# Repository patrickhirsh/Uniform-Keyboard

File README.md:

# Uniform65 Keyboard
A custom semi-ortholinear stabless mechanical keyboard

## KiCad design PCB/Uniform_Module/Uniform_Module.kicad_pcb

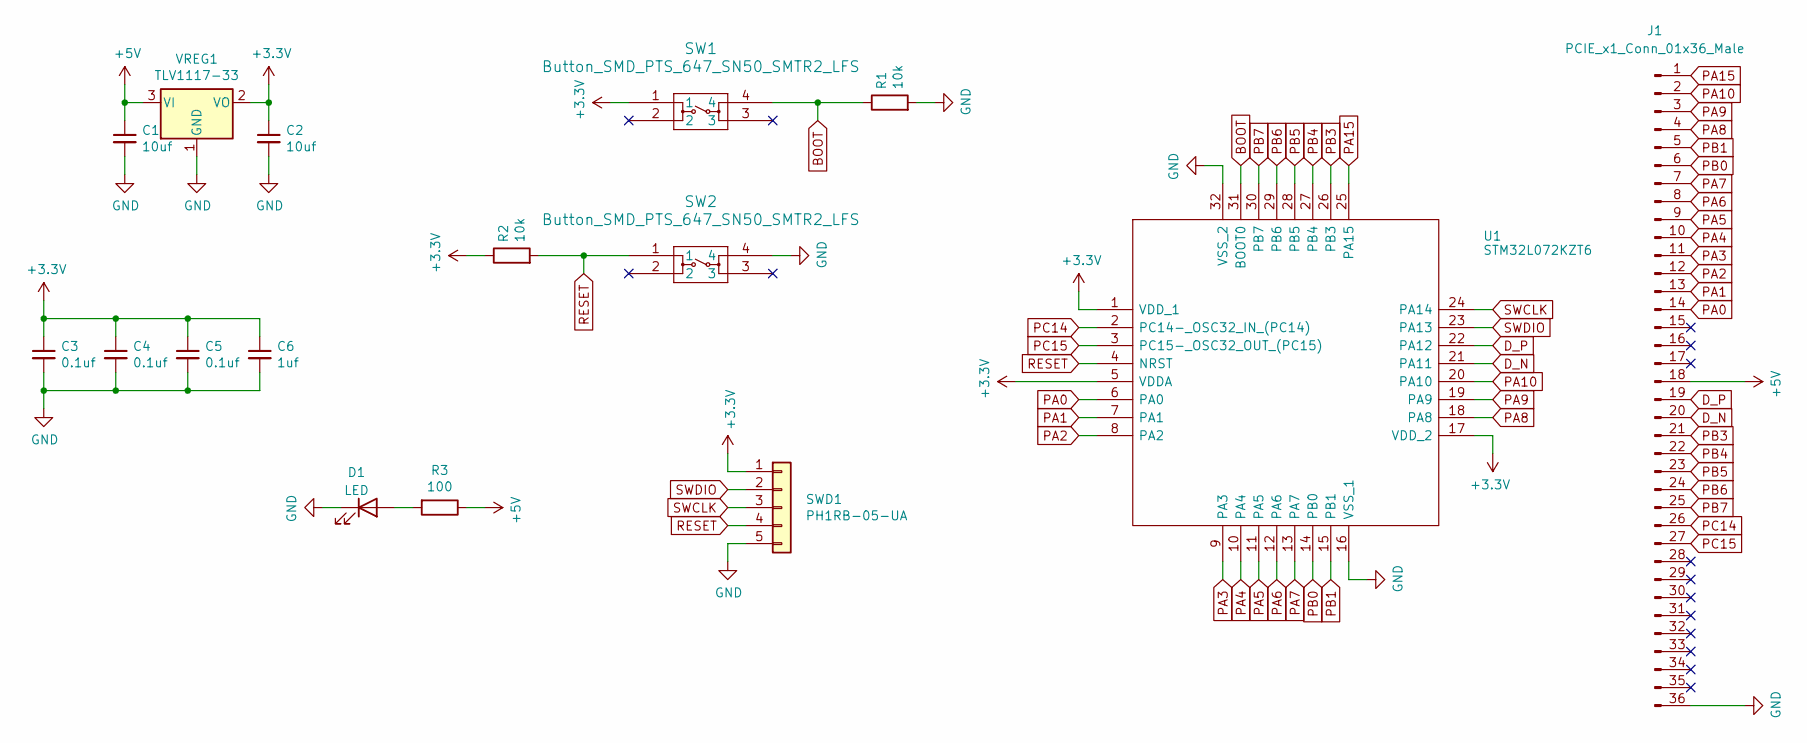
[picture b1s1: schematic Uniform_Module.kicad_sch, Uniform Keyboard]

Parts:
C1, C2: 10uf; C_0603_1608Metric_Pad1.08x0.95mm_HandSolder
C3, C4, C5: 0.1uf; C_0603_1608Metric_Pad1.08x0.95mm_HandSolder
C6: 1uf; C_0603_1608Metric_Pad1.08x0.95mm_HandSolder
D1: LED; LED_0603_1608Metric_Pad1.05x0.95mm_HandSolder
J1: PCIE_x1_Conn_01x36_Male; SAMTEC_PCIE_x1_CARD_EDGE_02_X_D_TH
R1, R2: 10k; R_0603_1608Metric_Pad0.98x0.95mm_HandSolder
R3: 100; R_0603_1608Metric_Pad0.98x0.95mm_HandSolder
SW1, SW2: Button_SMD_PTS_647_SN50_SMTR2_LFS; Button SMD PTS 647 SN50 SMTR2 LFS
SWD1: PH1RB-05-UA; PinHeader_1x05_P2.54mm_Vertical
U1: STM32L072KZT6; QFP80P900X900X160-32N; Mouser Part Number 511-STM32L072KZT6
VREG1: TLV1117-33; SOT230P700X180-4N

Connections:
+3V3: C2.1, C3.1, C4.1, C5.1, C6.1, R2.1, SW1.1, SWD1.1, U1.1 (VDD_1), U1.5 (VDDA), U1.17 (VDD_2), VREG1.2 (VO)
+5V: C1.1, J1.18, R3.1, VREG1.3 (VI)
BOOT: R1.1, SW1.4, U1.31 (BOOT0)
D_N: J1.20, U1.21 (PA11)
D_P: J1.19, U1.22 (PA12)
GND: C1.2, C2.2, C3.2, C4.2, C5.2, C6.2, D1.1 (K), J1.36, R1.2, SW2.4, SWD1.5, U1.16 (VSS_1), U1.32 (VSS_2), VREG1.1 (GND)
unnamed: D1.2 (A), R3.2
PA0: J1.14, U1.6 (PA0)
PA1: J1.13, U1.7 (PA1)
PA2: J1.12, U1.8 (PA2)
PA3: J1.11, U1.9 (PA3)
PA4: J1.10, U1.10 (PA4)
PA5: J1.9, U1.11 (PA5)
PA6: J1.8, U1.12 (PA6)
PA7: J1.7, U1.13 (PA7)
PA8: J1.4, U1.18 (PA8)
PA9: J1.3, U1.19 (PA9)
PA10: J1.2, U1.20 (PA10)
PA15: J1.1, U1.25 (PA15)
PB0: J1.6, U1.14 (PB0)
PB1: J1.5, U1.15 (PB1)
PB3: J1.21, U1.26 (PB3)
PB4: J1.22, U1.27 (PB4)
PB5: J1.23, U1.28 (PB5)
PB6: J1.24, U1.29 (PB6)
PB7: J1.25, U1.30 (PB7)
PC14: J1.26, U1.2 (PC14-_OSC32_IN_(PC14))
PC15: J1.27, U1.3 (PC15-_OSC32_OUT_(PC15))
RESET: R2.2, SW2.1, SWD1.4, U1.4 (NRST)
SWCLK: SWD1.3, U1.24 (PA14)
SWDIO: SWD1.2, U1.23 (PA13)

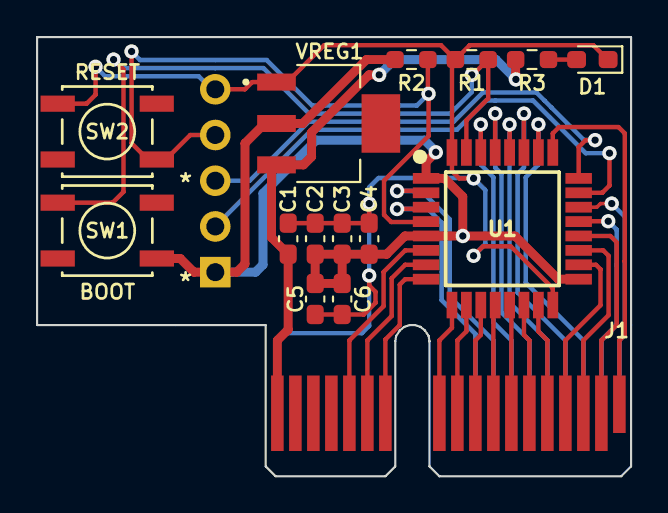
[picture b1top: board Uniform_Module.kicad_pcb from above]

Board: 2 copper layers, 33.0 x 24.4 mm, 16 parts (1 on the bottom side), 31 nets.

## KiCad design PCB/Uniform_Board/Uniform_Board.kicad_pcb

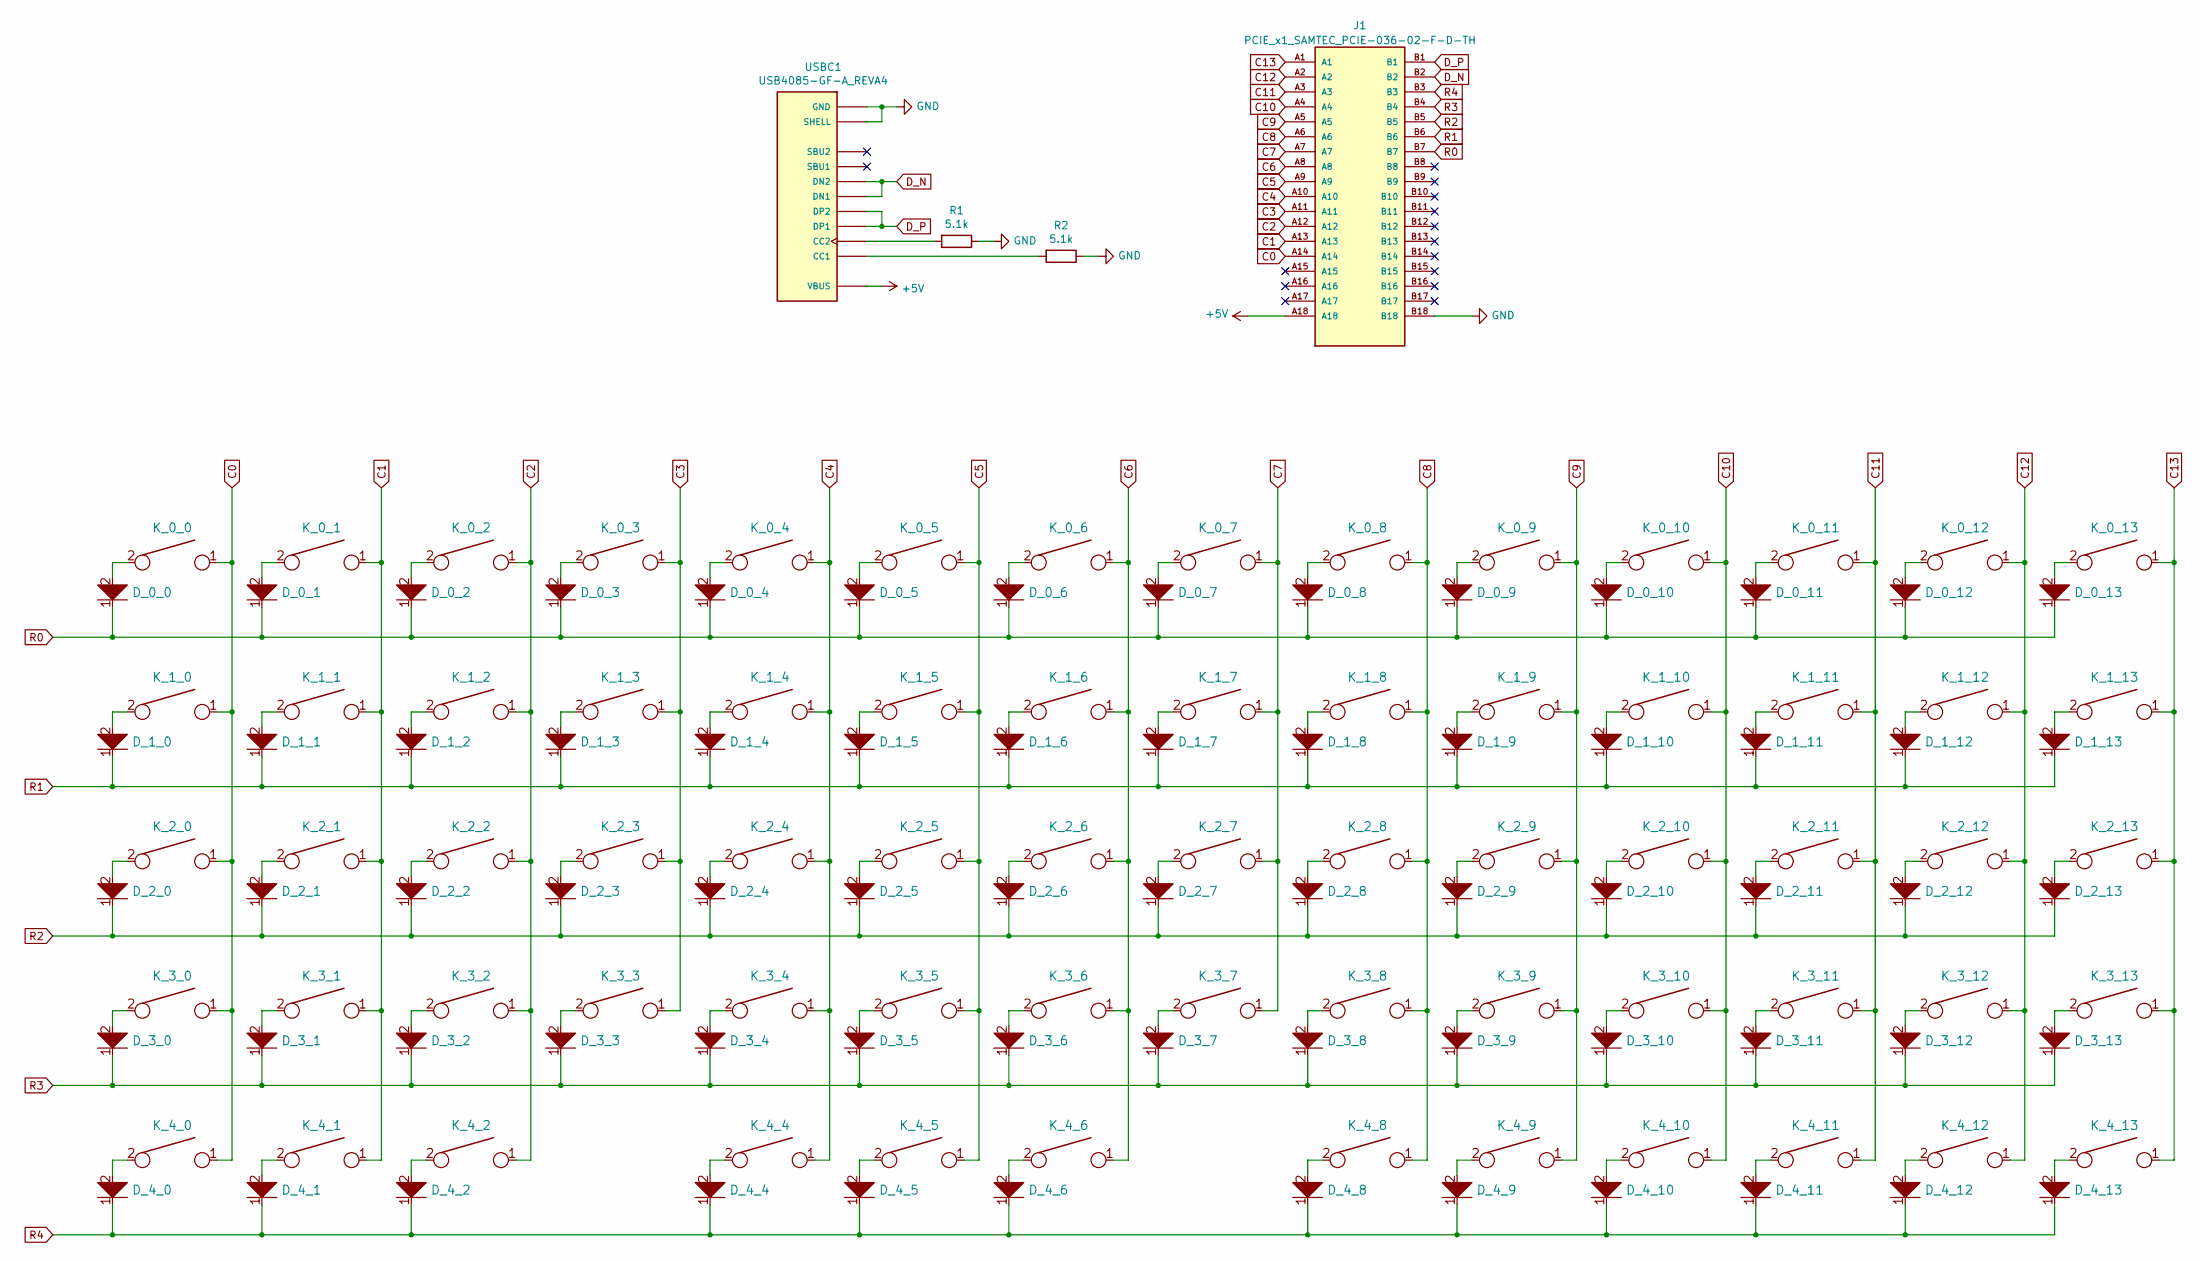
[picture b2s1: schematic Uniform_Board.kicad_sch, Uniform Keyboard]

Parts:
D_0_0, D_0_1, D_0_2, D_0_3, D_0_4, D_0_5, D_0_6, D_0_7, D_0_8, D_0_9, D_0_10, D_0_11, D_0_12, D_0_13, D_1_0, D_1_1, D_1_2, D_1_3, D_1_4, D_1_5, D_1_6, D_1_7, D_1_8, D_1_9, D_1_10, D_1_11, D_1_12, D_1_13, D_2_0, D_2_1, D_2_2, D_2_3, D_2_4, D_2_5, D_2_6, D_2_7, D_2_8, D_2_9, D_2_10, D_2_11, D_2_12, D_2_13, D_3_0, D_3_1, D_3_2, D_3_3, D_3_4, D_3_5, D_3_6, D_3_7, D_3_8, D_3_9, D_3_10, D_3_11, D_3_12, D_3_13, D_4_0, D_4_1, D_4_2, D_4_4, D_4_5, D_4_6, D_4_8, D_4_9, D_4_10, D_4_11, D_4_12, D_4_13: D; Diode_DIOAD829W49L456D191
J1: PCIE_x1_SAMTEC_PCIE-036-02-F-D-TH; SAMTEC_PCIE-036-02-F-D-TH
K_0_0, K_0_1, K_0_2, K_0_3, K_0_4, K_0_5, K_0_6, K_0_7, K_0_8, K_0_9, K_0_10, K_0_11, K_0_12, K_0_13, K_1_0, K_1_1, K_1_2, K_1_3, K_1_4, K_1_5, K_1_6, K_1_7, K_1_8, K_1_9, K_1_10, K_1_11, K_1_12, K_1_13, K_2_0, K_2_1, K_2_2, K_2_3, K_2_4, K_2_5, K_2_6, K_2_7, K_2_8, K_2_9, K_2_10, K_2_11, K_2_12, K_2_13, K_3_0, K_3_1, K_3_2, K_3_3, K_3_4, K_3_5, K_3_6, K_3_7, K_3_8, K_3_9, K_3_10, K_3_11, K_3_12, K_3_13, K_4_0, K_4_1, K_4_2, K_4_4, K_4_5, K_4_6, K_4_8, K_4_9, K_4_10, K_4_11, K_4_12, K_4_13: KEYSW; SW_MX
R1, R2: 5.1k; R_0603_1608Metric_Pad0.98x0.95mm_HandSolder
USBC1: USB4085-GF-A_REVA4; USBC_USB4085-GF-A; PARTREV A4

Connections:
+5V: J1.A18, USBC1.A4 (VBUS), USBC1.A9 (VBUS), USBC1.B4 (VBUS), USBC1.B9 (VBUS)
C0: J1.A14, K_0_0.1, K_1_0.1, K_2_0.1, K_3_0.1, K_4_0.1
C1: J1.A13, K_0_1.1, K_1_1.1, K_2_1.1, K_3_1.1, K_4_1.1
C2: J1.A12, K_0_2.1, K_1_2.1, K_2_2.1, K_3_2.1, K_4_2.1
C3: J1.A11, K_0_3.1, K_1_3.1, K_2_3.1, K_3_3.1
C4: J1.A10, K_0_4.1, K_1_4.1, K_2_4.1, K_3_4.1, K_4_4.1
C5: J1.A9, K_0_5.1, K_1_5.1, K_2_5.1, K_3_5.1, K_4_5.1
C6: J1.A8, K_0_6.1, K_1_6.1, K_2_6.1, K_3_6.1, K_4_6.1
C7: J1.A7, K_0_7.1, K_1_7.1, K_2_7.1, K_3_7.1
C8: J1.A6, K_0_8.1, K_1_8.1, K_2_8.1, K_3_8.1, K_4_8.1
C9: J1.A5, K_0_9.1, K_1_9.1, K_2_9.1, K_3_9.1, K_4_9.1
C10: J1.A4, K_0_10.1, K_1_10.1, K_2_10.1, K_3_10.1, K_4_10.1
C11: J1.A3, K_0_11.1, K_1_11.1, K_2_11.1, K_3_11.1, K_4_11.1
C12: J1.A2, K_0_12.1, K_1_12.1, K_2_12.1, K_3_12.1, K_4_12.1
C13: J1.A1, K_0_13.1, K_1_13.1, K_2_13.1, K_3_13.1, K_4_13.1
D_N: J1.B2, USBC1.A7 (DN1), USBC1.B7 (DN2)
D_P: J1.B1, USBC1.A6 (DP1), USBC1.B6 (DP2)
GND: J1.B18, R1.1, R2.1, USBC1.A1 (GND), USBC1.A12 (GND), USBC1.B1 (GND), USBC1.B12 (GND), USBC1.P1 (SHELL), USBC1.P2 (SHELL), USBC1.P3 (SHELL), USBC1.P4 (SHELL)
unnamed: D_0_0.2, K_0_0.2
unnamed: D_0_1.2, K_0_1.2
unnamed: D_0_2.2, K_0_2.2
unnamed: D_0_3.2, K_0_3.2
unnamed: D_0_4.2, K_0_4.2
unnamed: D_0_5.2, K_0_5.2
unnamed: D_0_6.2, K_0_6.2
unnamed: D_0_7.2, K_0_7.2
unnamed: D_0_8.2, K_0_8.2
unnamed: D_0_9.2, K_0_9.2
unnamed: D_0_10.2, K_0_10.2
unnamed: D_0_11.2, K_0_11.2
unnamed: D_0_12.2, K_0_12.2
unnamed: D_0_13.2, K_0_13.2
unnamed: D_1_0.2, K_1_0.2
unnamed: D_1_1.2, K_1_1.2
unnamed: D_1_2.2, K_1_2.2
unnamed: D_1_3.2, K_1_3.2
unnamed: D_1_4.2, K_1_4.2
unnamed: D_1_5.2, K_1_5.2
unnamed: D_1_6.2, K_1_6.2
unnamed: D_1_7.2, K_1_7.2
unnamed: D_1_8.2, K_1_8.2
unnamed: D_1_9.2, K_1_9.2
unnamed: D_1_10.2, K_1_10.2
unnamed: D_1_11.2, K_1_11.2
unnamed: D_1_12.2, K_1_12.2
unnamed: D_1_13.2, K_1_13.2
unnamed: D_2_0.2, K_2_0.2
unnamed: D_2_1.2, K_2_1.2
unnamed: D_2_2.2, K_2_2.2
unnamed: D_2_3.2, K_2_3.2
unnamed: D_2_4.2, K_2_4.2
unnamed: D_2_5.2, K_2_5.2
unnamed: D_2_6.2, K_2_6.2
unnamed: D_2_7.2, K_2_7.2
unnamed: D_2_8.2, K_2_8.2
unnamed: D_2_9.2, K_2_9.2
unnamed: D_2_10.2, K_2_10.2
unnamed: D_2_11.2, K_2_11.2
unnamed: D_2_12.2, K_2_12.2
unnamed: D_2_13.2, K_2_13.2
unnamed: D_3_0.2, K_3_0.2
unnamed: D_3_1.2, K_3_1.2
unnamed: D_3_2.2, K_3_2.2
unnamed: D_3_3.2, K_3_3.2
unnamed: D_3_4.2, K_3_4.2
unnamed: D_3_5.2, K_3_5.2
unnamed: D_3_6.2, K_3_6.2
unnamed: D_3_7.2, K_3_7.2
unnamed: D_3_8.2, K_3_8.2
unnamed: D_3_9.2, K_3_9.2
unnamed: D_3_10.2, K_3_10.2
unnamed: D_3_11.2, K_3_11.2
unnamed: D_3_12.2, K_3_12.2
unnamed: D_3_13.2, K_3_13.2
unnamed: D_4_0.2, K_4_0.2
unnamed: D_4_1.2, K_4_1.2
unnamed: D_4_2.2, K_4_2.2
unnamed: D_4_4.2, K_4_4.2
unnamed: D_4_5.2, K_4_5.2
unnamed: D_4_6.2, K_4_6.2
unnamed: D_4_8.2, K_4_8.2
unnamed: D_4_9.2, K_4_9.2
unnamed: D_4_10.2, K_4_10.2
unnamed: D_4_11.2, K_4_11.2
unnamed: D_4_12.2, K_4_12.2
unnamed: D_4_13.2, K_4_13.2
unnamed: R1.2, USBC1.B5 (CC2)
unnamed: R2.2, USBC1.A5 (CC1)
R0: D_0_0.1, D_0_1.1, D_0_2.1, D_0_3.1, D_0_4.1, D_0_5.1, D_0_6.1, D_0_7.1, D_0_8.1, D_0_9.1, D_0_10.1, D_0_11.1, D_0_12.1, D_0_13.1, J1.B7
R1: D_1_0.1, D_1_1.1, D_1_2.1, D_1_3.1, D_1_4.1, D_1_5.1, D_1_6.1, D_1_7.1, D_1_8.1, D_1_9.1, D_1_10.1, D_1_11.1, D_1_12.1, D_1_13.1, J1.B6
R2: D_2_0.1, D_2_1.1, D_2_2.1, D_2_3.1, D_2_4.1, D_2_5.1, D_2_6.1, D_2_7.1, D_2_8.1, D_2_9.1, D_2_10.1, D_2_11.1, D_2_12.1, D_2_13.1, J1.B5
R3: D_3_0.1, D_3_1.1, D_3_2.1, D_3_3.1, D_3_4.1, D_3_5.1, D_3_6.1, D_3_7.1, D_3_8.1, D_3_9.1, D_3_10.1, D_3_11.1, D_3_12.1, D_3_13.1, J1.B4
R4: D_4_0.1, D_4_1.1, D_4_2.1, D_4_4.1, D_4_5.1, D_4_6.1, D_4_8.1, D_4_9.1, D_4_10.1, D_4_11.1, D_4_12.1, D_4_13.1, J1.B3

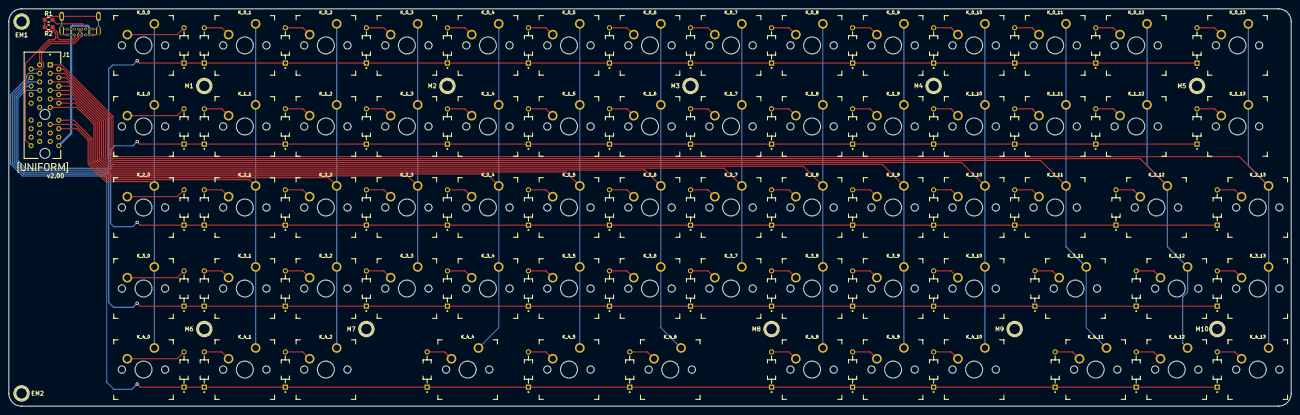
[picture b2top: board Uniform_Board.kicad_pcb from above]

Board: 2 copper layers, 301.5 x 93.4 mm, 152 parts (1 on the bottom side), 93 nets.

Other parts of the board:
EM1, EM2: MountingHole_2.7mm_M2.5
M1, M2, M3, M4, M5, M6, M7, M8, M9, M10: MountingHole_2.7mm_M2.5

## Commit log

2022-02-04 added layout schematic
2022-02-05 Added gaps in bottom row schematic
2022-02-06 added KiCad libraries and new reference material
2022-02-06 keyboard matrix schema finished
2022-02-06 added diode labels
2022-02-06 added crystal, voltage regulator, and boot/reset switches
2022-02-07 added usb module to schema
2022-02-07 mostly finished schema - need to select crystal and change flanking capacitor values accordingly
2022-02-08 Switched MCUs to STM32L072KZT6 because the F3 series went out of stock..
2022-02-09 Schematic complete
2022-02-09 switch footprints layed out on PCB
2022-02-10 finished board outline
2022-02-10 flipped exposed PCB side to make room for USBC pins
2022-02-10 full layout first pass
2022-02-10 Tweaking some things
2022-02-10 moved status LED to a better location
2022-02-16 updating project to KiCad 6.0
2022-02-16 Added traces for all key switches
2022-02-17 about to attempt rotating the MCU
2022-02-17 re-worked layout to reduce ratsnest crossover
2022-02-17 PCB first pass complete
2022-02-17 Added SWD silkscreen
2022-02-18 silkscreen artwork added
2022-02-18 fixed stray silkscreen text
2022-02-19 v1 final gerber files submitted
2022-02-19 changed M3 mounting to M2.5 due to clearance issues
2022-02-19 added mounting hole graphics
2022-05-01 Moved mount holes so the drill points in the plate won't collide with switch clip-in points
2022-05-05 revert ATMEGA32 changes to schematic that were lumped into last commit
2022-05-11 Added Neopixel status LED, moved mount holes, and re-routed traces to fit new status led type
2022-05-11 generated gerbers and finalized V2
2022-05-11 reduced neopixel pin drill hole size from .9 to .8 to accomodate typical minimum manufacturing hole spacing requirements
2022-05-30 Added 2 more Neopixels and supporting logic level shifter
2022-07-07 Move status LED resistor between the logic level shifter and the LED to fix flicker issue
2022-08-22 cleaning up references directory
2022-08-30 initial buildguide docs
2022-08-30 added Plate section
2022-08-30 build guide progress
2022-08-30 fixed typos and formatting
2022-08-31 Refined Prep and Assembly sections
2022-09-02 more buildguide content
2022-09-02 Add link to gerber files
2022-09-02 Added two more images
2022-09-02 rename image files
2022-09-03 Added new guide images
2022-09-03 switches and keycaps section, case section improvements with mounting information
2022-09-03 tweaked wording in Plate section
2022-09-03 add new images for plate drill holes and tofu65 mounting
2022-09-03 Tofu65 Mounting
2022-09-03 Tofu65 example
2022-09-03 added new Tofu65 example photo
2022-09-03 Tofu65 Example 2
2022-09-03 Tofu65 Mounting Example 2
2022-09-03 Plate section formatting
2022-09-03 Fix Tofu65 filenames
2022-09-03 Add plate drill hole example
2022-09-03 Added mount screw access holes example to Plate section
2022-09-03 add plate svg to plate section
2022-09-03 fix image name for plate file
2022-09-03 move plate image position in plate section
2022-09-03 Fix list spacing in PCB Assembly section
2022-09-03 fixed typo in 10u cap image
2024-02-17 move old libraries to 'legacy' and create new library for non-legacy symbols
2024-02-18 broke Uniform into two projects - uniform_board and uniform_module. Finished uniform_module schematic
2024-02-18 completed uniform_board schematic
2024-02-19 board USBC and power routed to PCIE, pre row/column routing
2024-02-19 started board routing; first attempt
2024-02-19 rework routing on board, cleaner!
2024-02-19 finished uniform board routing
2024-02-19 fixed some minor routing issues on uniform board, removed silkscreen diode ref text
2024-02-19 finishing touches on silkscreen graphics for board
2024-02-20 PCIE slot is upside down... began footprint, comitting changes and preparing to re-route on board :(
2024-02-26 PCIE Edge Connector footprint dimmensions and edge cuts done
2024-02-28 began routing for uniform module
2024-02-28 clear all routing on module. Fix incorrect PCIE edge connector schematic net assignments
2024-02-29 improved trace origins on PCIE port/edge. Board rerouting done. Module rerouting in progress
2024-02-29 first pass at module layout. silkscreen added
2024-02-29 uniform module routing half done
2024-03-03 Uniform module traces first pass complete
2024-03-03 Uniform Module passing DRC
2024-03-03 silkscreen work and minor tweaks to uniform module board
